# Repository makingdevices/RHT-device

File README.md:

<!-- Improved compatibility of back to top link: See: https://github.com/othneildrew/Best-README-Template/pull/73 -->

<!--
*** Thanks for checking out the Best-README-Template. If you have a suggestion
*** that would make this better, please fork the repo and create a pull request
*** or simply open an issue with the tag "enhancement".
*** Don't forget to give the project a star!
*** Thanks again! Now go create something AMAZING! :D
-->

<!-- PROJECT SHIELDS -->
<!--
*** I'm using markdown "reference style" links for readability.
*** Reference links are enclosed in brackets [ ] instead of parentheses ( ).
*** See the bottom of this document for the declaration of the reference variables
*** for contributors-url, forks-url, etc. This is an optional, concise syntax you may use.
*** https://www.markdownguide.org/basic-syntax/#reference-style-links
-->
[![Instagram][ig-shield]][ig-url]
[![PCBWAY][sponsor-shield]][sponsor-url]
[![Stargazers][stars-shield]][stars-url]
[![Issues][issues-shield]][issues-url]
[![LinkedIn][linkedin-shield]][linkedin-url]

<!-- PROJECT LOGO -->
<br />
<div align="center">

<h3 align="center">Making Devices</h3>

  <p align="center">
    Open Source projects where we struggle with engineering, electronics, coding and who knows what else... In this case, RHT Device is a very simple humidity and temperature sensor, so hopefully you may find it interesting ;)
  </p>
</div>

<!-- TABLE OF CONTENTS -->
<details>
  <summary>Table of Contents</summary>
  <ol>
    <li>
      <a href="#about-the-project">About The Project</a>
      <ul>
        <li><a href="#built-with">Built With</a></li>
      </ul>
    </li>
    <li>
      <a href="#Build-one">Build one</a>
      <ul>
      </ul>
    </li>
    <li><a href="#usage">Usage</a></li>
    <li><a href="#roadmap">Roadmap</a></li>
    <li><a href="#license">License</a></li>
    <li><a href="#contact">Contact</a></li>
    <li><a href="#Sponsor">Sponsor</a></li>
  </ol>
</details>

<!-- ABOUT THE PROJECT -->
## About The Project

[![Bytes Counter Shot][product-screenshot]](https://github.com/makingdevices/RHT-device)

RHT Device is a very simple relative humidity and temperature sensor that shows the data in the screen. The project was chosen to test the I2C communication of the PIC18F14k50. 

<p align="right">(<a href="#readme-top">back to top</a>)</p>

### Built With

[![Microcontroller][PIC]][PIC-url]
[![MPLAB C][MPLAB-C]][MPLAB-C-url]
[![Kicad][kicad-shield]][kicad-url]
[![SPONSOR][sponsor-icon]][sponsor-url]

<p align="right">(<a href="#readme-top">back to top</a>)</p>

<!-- GETTING STARTED -->

## Build one
Documentation is being updated.

1. Get the gerber files for the latest version: [V1.0](https://github.com/makingdevices/RHT-device/tree/main/Gerber/Gerber_v1.0.zip) 
2. Send them to a PCB manufacturer ([Our Sponsor is PCBWAY][sponsor-url])
3. You should solder all the components in the board. ([The schematic is available here v1.0][schematic-url])
4. Program the firmware into the pic. ([V1.0 is here][firmware-url])

Enjoy :)

<p align="right">(<a href="#readme-top">back to top</a>)</p>

<!-- USAGE EXAMPLES -->
## Usage

Instructions of use:

- When the button is pressed, the temperature is shown.
- Next time the button is pressed, relative humidity is shown. It will change between temperature and humidity
- After 10s of no use, the screen will be off and the device enters sleep mode.
- One button click will wake up the device for another 10s

<p align="right">(<a href="#readme-top">back to top</a>)</p>

<!-- ROADMAP -->
## Roadmap

- [x] Finish the firmware for the PIC18F14K50
- [x] Validate the RHT-Device board V1.0
- [x] Update all the documentation

See the [open issues](https://github.com/makingdevices/RHT-device/issues) for a full list of proposed features (and known issues).

State: Project <b>FINISHED</b> - 11/05/2023

<p align="right">(<a href="#readme-top">back to top</a>)</p>

<!-- Power Consumption -->
## Power Consumption

One of the main requisites for the board is to obtain a minimum power consumption so the device can live from a coin cell. When the screen is on we obtain:

[![ON Screen consumption Shot][pconscreen-screenshot]](https://github.com/makingdevices/RHT-device/tree/main/Validation/)

<b>Average Current</b> = 10.69mA

In sleep mode, the power consumption is as follows:

[![OFF Screen consumption Shot][pcoffscreen-screenshot]](https://github.com/makingdevices/RHT-device/tree/main/Validation/)

<b>Average Current</b> = 6.79uA

With this data and a normal use of 5 reading a day, the battery should last for several years.

<p align="right">(<a href="#readme-top">back to top</a>)</p>

<!-- LICENSE -->
## License

Distributed under three licenses:
- [Hardware](/License/HW_cern_ohl_s_v2.pdf)
- [Software](/License/SW_GPLv3.0.txt)
- [Documentation](/License/Documentation_CC-BY-SA-4.0.txt)

[![GPL v3 License][license-shield]][license-url] 
<p align="right">(<a href="#readme-top">back to top</a>)</p>

<!-- CONTACT -->
## Contact

Making Devices - [@MakingDevices](https://www.instagram.com/makingdevices/)

Project Link: [https://github.com/makingdevices/Thermo-device-logger](https://github.com/makingdevices/RHT-device/)

Other Links: [LinkTree](https://makingdevices.com/links/)

<p align="right">(<a href="#readme-top">back to top</a>)</p>

<!-- Sponsor -->
## Sponsor

[PCBWAY](https://www.pcbway.com/?from=makingdevices) is the most professional PCB manufacturer for prototyping and low-volume production to work with in the world. With more than a decade in the field, They are committed to meeting the needs of their customers from different industries in terms of quality, delivery, cost-effectiveness and any other demanding requests. As Sponsor of Making Devices, they will be in charge of all the PCBs for MDV, allowing both of us to grow together in a long term partnership. We hope you take them into account for your both personal and professional prototypes or products.

[![Sponsor Shot][sponsor-screenshot-pcb1]][sponsor-url]
[![Sponsor Shot][sponsor-screenshot-pcb2]][sponsor-url]

<p align="right">(<a href="#readme-top">back to top</a>)</p>

<!-- MARKDOWN LINKS & IMAGES -->
<!-- https://www.markdownguide.org/basic-syntax/#reference-style-links -->
[contributors-shield]: https://img.shields.io/github/contributors/makingdevices/RHT-device.svg?style=for-the-badge
[contributors-url]: https://github.com/makingdevices/RHT-device/graphs/contributors
[forks-shield]: https://img.shields.io/github/forks/makingdevices/RHT-device.svg?style=for-the-badge
[forks-url]: https://github.com/makingdevices/RHT-device/network/members
[stars-shield]: https://img.shields.io/github/stars/makingdevices/RHT-device.svg?style=for-the-badge
[stars-url]: https://github.com/makingdevices/RHT-device/stargazers
[issues-shield]: https://img.shields.io/github/issues/makingdevices/RHT-device.svg?style=for-the-badge
[issues-url]: https://github.com/makingdevices/RHT-device/issues
[license-shield]: /images/license.png
[license-url]: https://github.com/makingdevices/RHT-device/tree/main/License
[linkedin-shield]: https://img.shields.io/badge/-LinkedIn-black.svg?style=for-the-badge&logo=linkedin&colorB=555
[linkedin-url]: https://www.linkedin.com/company/making-devices/
[sponsor-shield]: https://img.shields.io/badge/SPONSOR-PCBWAY-black.svg?style=for-the-badge&colorB=1200
[sponsor-url]: https://www.pcbway.com/?from=makingdevices
[sponsor-screenshot-pcb1]: /images/rht_pcb1.jpg
[sponsor-screenshot-pcb2]: /images/rht_pcb2.jpg
[product-screenshot]: images/screenshotV1.0.gif
[pconscreen-screenshot]: /Validation/4_Power_Consumption/Screen_ON.png
[pcoffscreen-screenshot]: /Validation/4_Power_Consumption/Screen_OFF.png
[PIC]: https://img.shields.io/badge/PIC18LF14K50-000000?style=for-the-badge
[PIC-url]: http://ww1.microchip.com/downloads/en/devicedoc/40001350f.pdf
[kicad-shield]: https://img.shields.io/badge/kicad-0b03fc?style=for-the-badge&logo=kicad&logoColor=white
[kicad-url]: https://www.kicad.org/
[YT-screenshot]: images/YT_assembly.PNG
[sponsor-icon]:  https://img.shields.io/badge/-PCBWAY-black.svg?style=for-the-badge&colorB=1200
[ig-shield]: https://img.shields.io/badge/instagram-a83297?style=for-the-badge&logo=instagram&logoColor=white
[ig-url]: https://www.instagram.com/makingdevices/
[MPLAB-C]: https://img.shields.io/badge/MPLAB%20C18-DD0031?style=for-the-badge&logo=C&logoColor=white
[MPLAB-C-url]: https://www.microchip.com/en-us/development-tool/SW006011
[Svelte.dev]: https://img.shields.io/badge/Svelte-4A4A55?style=for-the-badge&logo=svelte&logoColor=FF3E00
[Svelte-url]: https://svelte.dev/
[Laravel.com]: https://img.shields.io/badge/Laravel-FF2D20?style=for-the-badge&logo=laravel&logoColor=white
[Laravel-url]: https://laravel.com
[Bootstrap.com]: https://img.shields.io/badge/Bootstrap-563D7C?style=for-the-badge&logo=bootstrap&logoColor=white
[Bootstrap-url]: https://getbootstrap.com
[JQuery.com]: https://img.shields.io/badge/jQuery-0769AD?style=for-the-badge&logo=jquery&logoColor=white
[JQuery-url]: https://jquery.com 
[schematic-url]: /Output_PDF/Schematic_v1.0.pdf
[firmware-url]: /Firmware/RHT-device.hex

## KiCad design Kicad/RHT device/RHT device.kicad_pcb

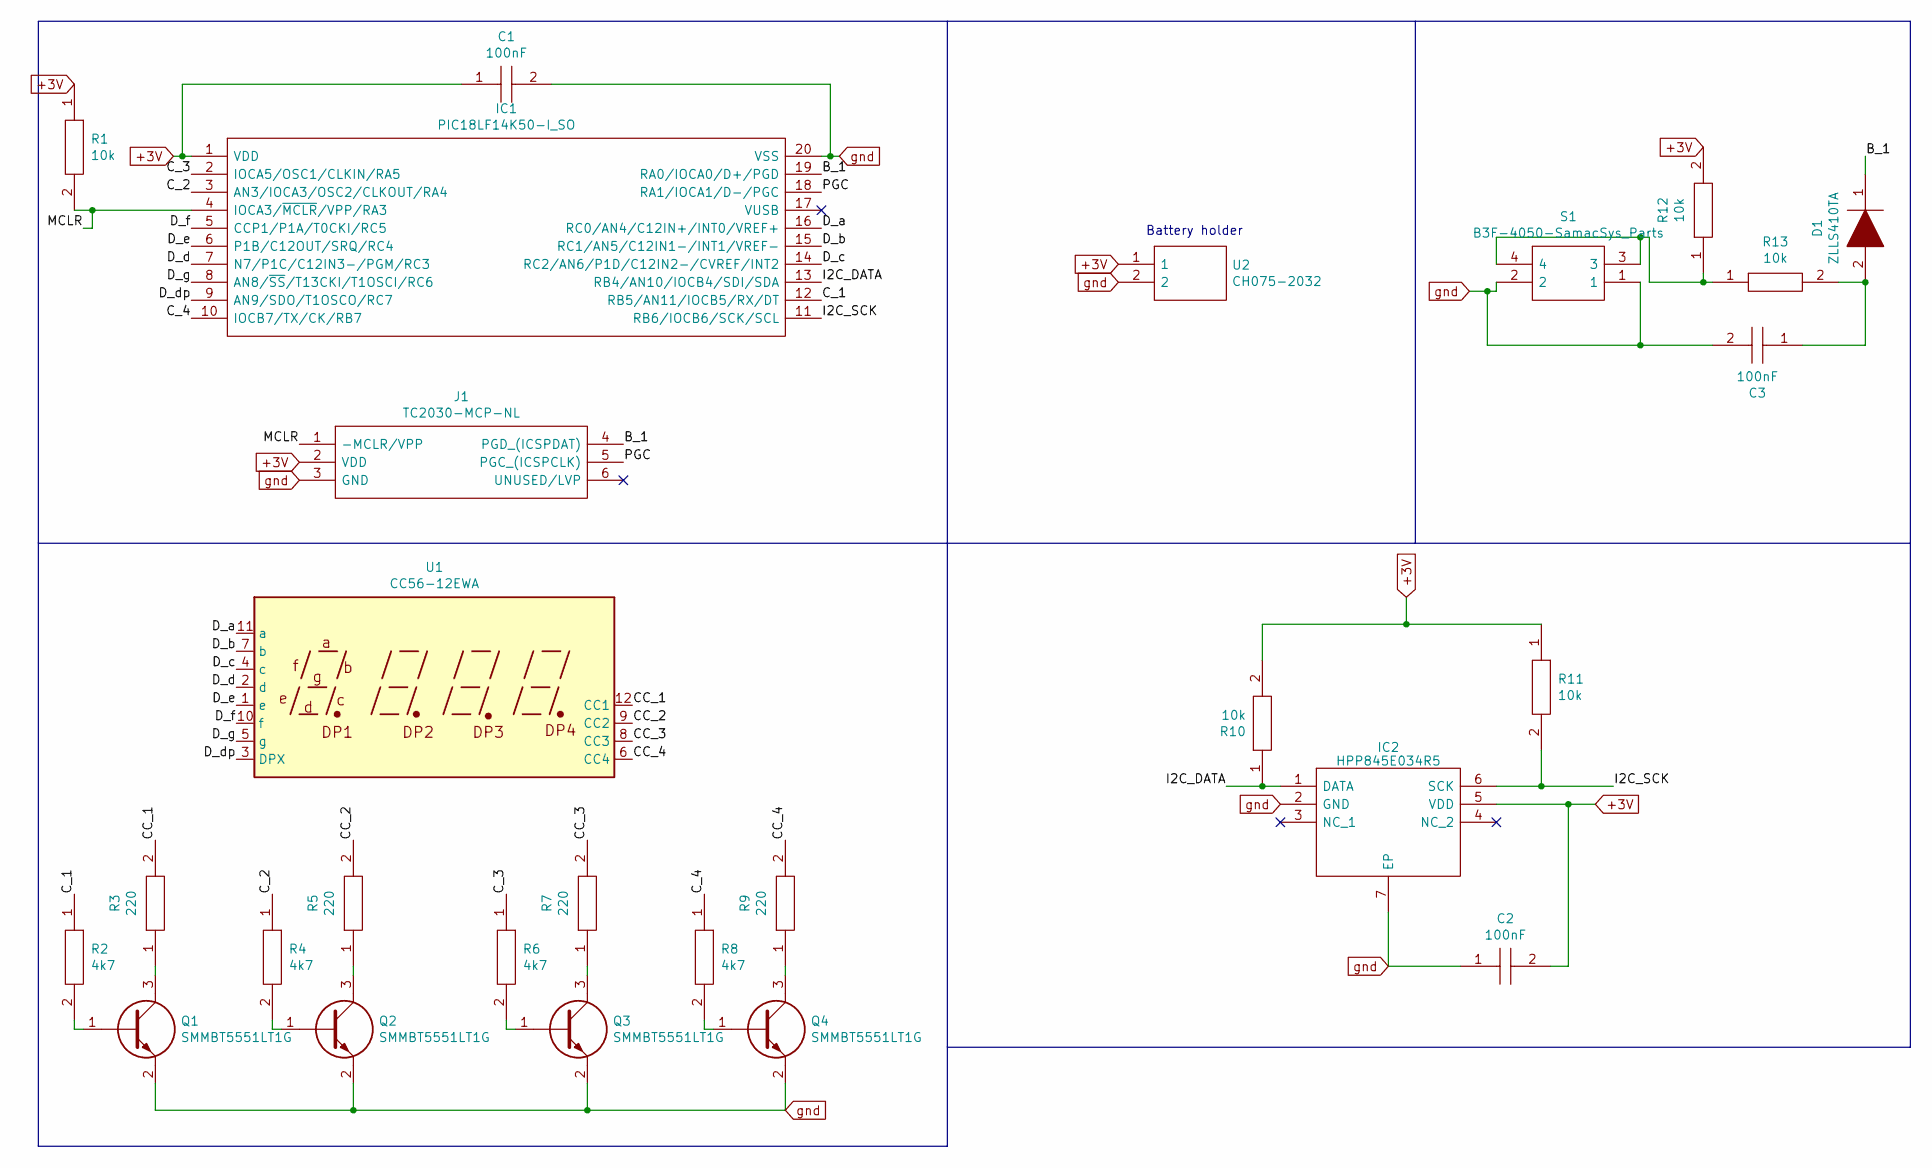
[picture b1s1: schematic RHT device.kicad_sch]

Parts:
C1, C2, C3: 100nF; CAPC2012X140N; Manufacturer_Part_Number C0805C475M8RACTU
D1: ZLLS410TA; SOD2513X120N; Manufacturer_Part_Number ZLLS410TA
IC1: PIC18LF14K50-I_SO; SSOP-20_5.3x7.2mm_P0.65mm; Manufacturer_Part_Number PIC18LF14K50-I/SO
IC2: HPP845E034R5; SON100P300X300X100-7N; Manufacturer_Part_Number HPP845E034R5; Mouser Part Number 824-HPP845E034R5
J1: TC2030-MCP-NL; Manufacturer_Part_Number TC2030-MCP-NL
Q1, Q2, Q3, Q4: SMMBT5551LT1G; SOT96P237X111-3N; Manufacturer_Part_Number SMMBT5551LT1G
R1, R10, R11, R12, R13: 10k; RESC2012X75N; Manufacturer_Part_Number ERJP6WF1303V
R2, R4, R6, R8: 4k7; RESC2012X75N; Manufacturer_Part_Number ERJP6WF1303V
R3, R5, R7, R9: 220; RESC2012X75N; Manufacturer_Part_Number ERJP6WF1303V
S1: B3F-4050-SamacSys_Parts; B3F4050; Manufacturer_Part_Number B3F-4050; Mouser Part Number 653-B3F-4050
U1: CC56-12EWA; CA56-12EWA
U2: CH075-2032; CH0752032; Manufacturer_Part_Number CH075-2032

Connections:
+3V: C1.1, C2.2, IC1.1 (VDD), IC2.5 (VDD), J1.2 (VDD), R1.1, R10.2, R11.1, R12.2, U2.1
/B_1: D1.1, IC1.19 (RA0/IOCA0/D+/PGD), J1.4 (PGD_(ICSPDAT))
/CC_1: R3.2, U1.12 (CC1)
/CC_2: R5.2, U1.9 (CC2)
/CC_3: R7.2, U1.8 (CC3)
/CC_4: R9.2, U1.6 (CC4)
/C_1: IC1.12 (RB5/AN11/IOCB5/RX/DT), R2.1
/C_2: IC1.3 (AN3/IOCA3/OSC2/CLKOUT/RA4), R4.1
/C_3: IC1.2 (IOCA5/OSC1/CLKIN/RA5), R6.1
/C_4: IC1.10 (IOCB7/TX/CK/RB7), R8.1
/D_a: IC1.16 (RC0/AN4/C12IN+/INT0/VREF+), U1.11 (a)
/D_b: IC1.15 (RC1/AN5/C12IN1-/INT1/VREF-), U1.7 (b)
/D_c: IC1.14 (RC2/AN6/P1D/C12IN2-/CVREF/INT2), U1.4 (c)
/D_d: IC1.7 (N7/P1C/C12IN3-/PGM/RC3), U1.2 (d)
/D_dp: IC1.9 (AN9/SDO/T1OSCO/RC7), U1.3 (DPX)
/D_e: IC1.6 (P1B/C12OUT/SRQ/RC4), U1.1 (e)
/D_f: IC1.5 (CCP1/P1A/T0CKI/RC5), U1.10 (f)
/D_g: IC1.8 (AN8/~SS/T13CKI/T1OSCI/RC6), U1.5 (g)
/I2C_DATA: IC1.13 (RB4/AN10/IOCB4/SDI/SDA), IC2.1 (DATA), R10.1
/I2C_SCK: IC1.11 (RB6/IOCB6/SCK/SCL), IC2.6 (SCK), R11.2
/MCLR: IC1.4 (IOCA3/~MCLR/VPP/RA3), J1.1 (-MCLR/VPP), R1.2
/PGC: IC1.18 (RA1/IOCA1/D-/PGC), J1.5 (PGC_(ICSPCLK))
unnamed: C3.1, D1.2, R13.2
unnamed: Q1.1, R2.2
unnamed: Q1.3, R3.1
unnamed: Q2.1, R4.2
unnamed: Q2.3, R5.1
unnamed: Q3.1, R6.2
unnamed: Q3.3, R7.1
unnamed: Q4.1, R8.2
unnamed: Q4.3, R9.1
unnamed: R12.1, R13.1, S1.3, S1.4
gnd: C1.2, C2.1, C3.2, IC1.20 (VSS), IC2.2 (GND), IC2.7 (EP), J1.3 (GND), Q1.2, Q2.2, Q3.2, Q4.2, S1.1, S1.2, U2.2

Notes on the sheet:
Battery holder

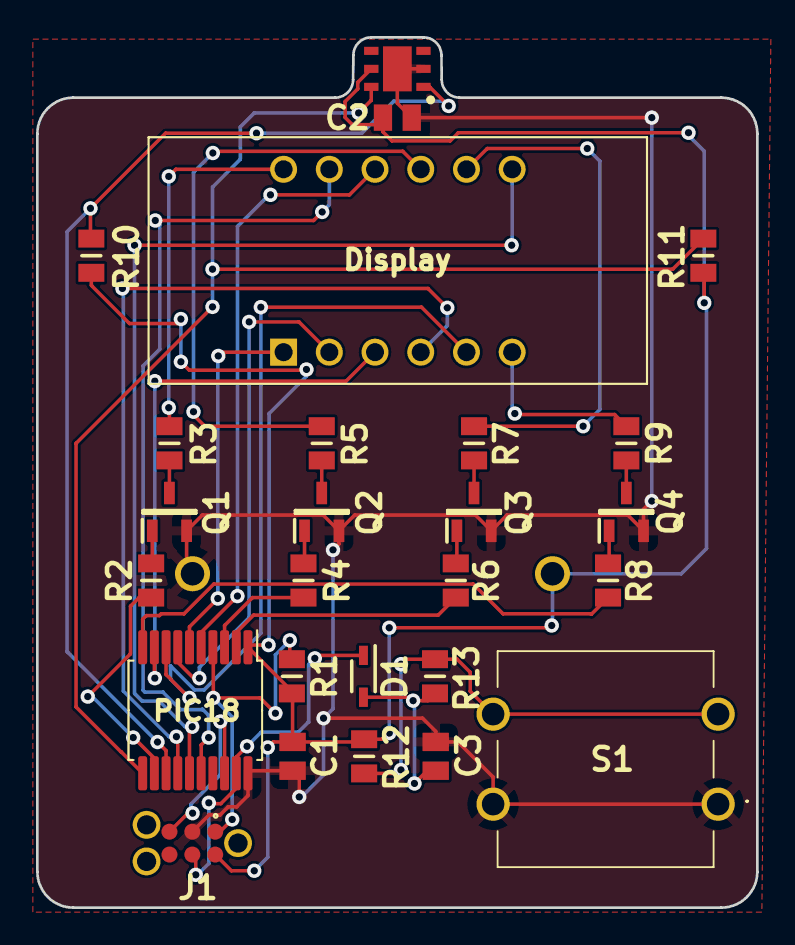
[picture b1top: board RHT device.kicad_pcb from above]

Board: 2 copper layers, 40.0 x 48.4 mm, 27 parts (1 on the bottom side), 33 nets.

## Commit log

2023-01-06 Update files
2023-01-06 Updates to the readme
2023-01-07 no message
2023-04-15 New firmware
2023-04-19 New HW version 1.0
2023-05-11 V1.0 files
2023-05-11 Validation folder. New firmware
2023-05-11 readme
2023-05-16 V1.0 version is finished
2023-05-16 Power consumption
2023-05-16 New documentation
2023-05-16 V1.0 documentation update
2023-08-02 Routing
